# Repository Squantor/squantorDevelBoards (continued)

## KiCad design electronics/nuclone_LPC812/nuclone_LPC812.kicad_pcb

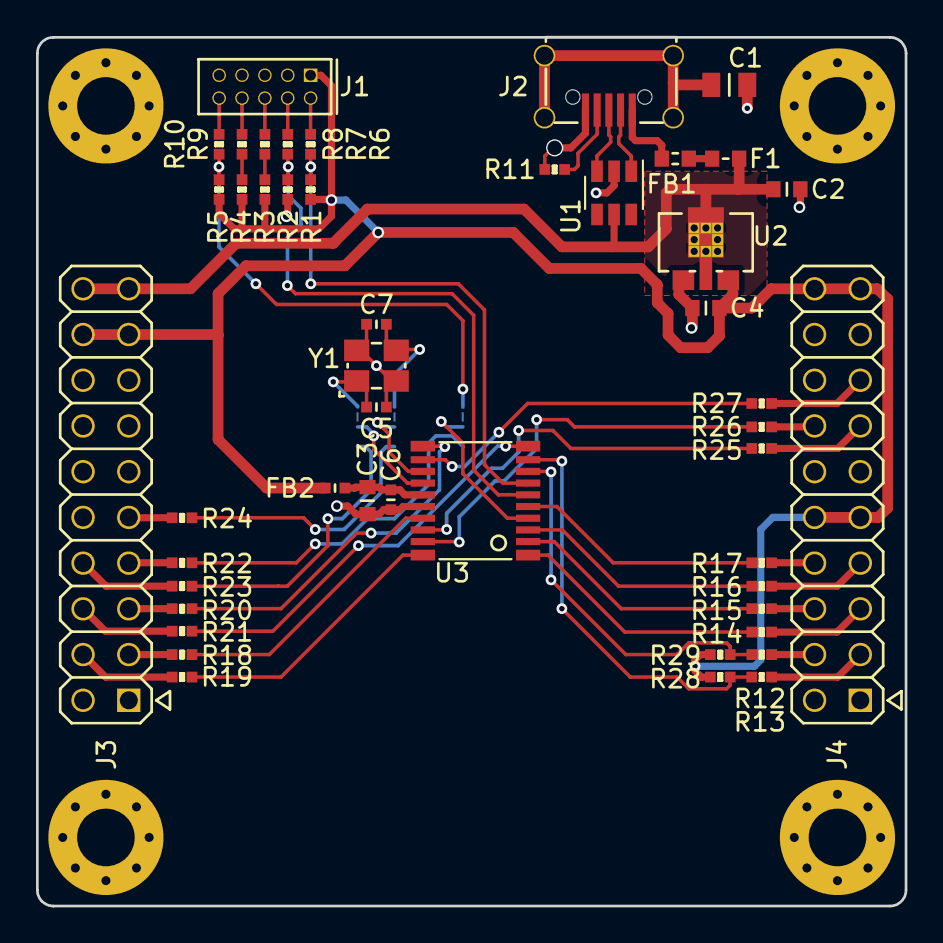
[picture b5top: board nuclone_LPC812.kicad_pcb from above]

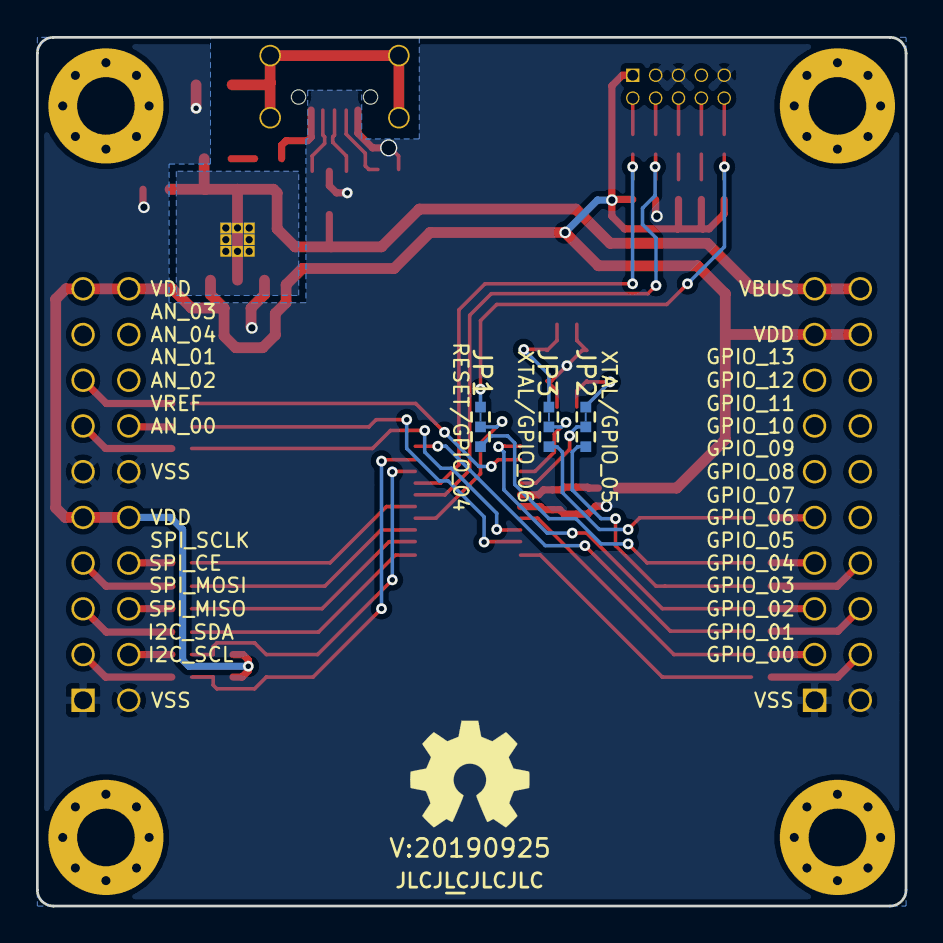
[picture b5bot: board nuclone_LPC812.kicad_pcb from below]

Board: 2 copper layers, 48.3 x 48.3 mm, 57 parts (6 on the bottom side), 57 nets.

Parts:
C1: 100n; C_0805
C2, C3, C4: 10u; C_0603
C5, C7: 18p; C_0402
C6: 1u; C_0402
F1: 0.5A; F_0603_hand
FB1: 100; L_0603
FB2: FB; C_0402
H1, H2, H3, H4: MountingHole; MountingHole_3.2mm_M3_Pad_Via
J1: JTAG_2X05; Header-0127-2X05-H006
J2: USB-ID; USB-muB-SMD_TH
J3: nuclone_20pin_gpio; Nuclone_20pin_gpio
J4: nuclone_20pin_bus_analog; Nuclone_20pin_bus_analog
JP1: RESET/GPIO_04; solder_jumper_3way_23conn
JP2: XTAL/GPIO_05; solder_jumper_3way_23conn
JP3: XTAL/GPIO_06; solder_jumper_3way_23conn
N1: OHWLOGO; OSHW-Symbol_6.7x6mm_SilkScreen
N2: 20190925; Label_version
N3: JLCJLCJLCJLC; Label_Generic
R1, R4: 100K; R_0402_hand
R2, R3, R5: 100k; R_0402_hand
R6, R7, R8, R9, R10, R12, R13, R14, R15, R16, R17, R18, R19, R20, R21, R22, R23, R24, R25, R26, R27: 100; R_0402_hand
R11: 0; R_0402_hand
R28, R29: 2.2K; R_0402_hand
U1: USBLC6-2; SOT23-6-HAND
U2: MCP1702-MB; SOT89-SOT23-Dual-NXP
U3: LPC812M101JDH20; SOT360
Y1: 12MHz; Crystal_3225_4

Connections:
/AN_00: J4.14, R26.2
/AN_01: J4.15, R27.2
/GPIO_00: J3.3, R18.2
/GPIO_01: J3.4, R19.2
/GPIO_02: J3.5, R20.2
/GPIO_03: J3.6, R21.2
/GPIO_04: J3.7, R22.2
/GPIO_05: J3.8, R23.2
/GPIO_06: J3.9, R24.2
/I2C_SCL: J4.4, R13.2
/I2C_SDA: J4.3, R12.2
/Jtag connector/TDI: R4.2, R9.2
/LPC812M101JD20 base/GPIO_04_INT: JP1.1, R22.1
/LPC812M101JD20 base/GPIO_05_INT: JP2.1, R23.1
/LPC812M101JD20 base/GPIO_06_INT: JP3.1, R24.1
/LPC812M101JD20 base/PIO0_0: R26.1, U3.19
/LPC812M101JD20 base/PIO0_1: R27.1, U3.12
/LPC812M101JD20 base/PIO0_4: R17.1, U3.5
/LPC812M101JD20 base/PIO0_5: JP1.2, U3.4
/LPC812M101JD20 base/PIO0_6: R25.1, U3.18
/LPC812M101JD20 base/PIO0_7: R18.1, U3.17
/LPC812M101JD20 base/PIO0_8: JP2.2, U3.14
/LPC812M101JD20 base/PIO0_9: JP3.2, U3.13
/LPC812M101JD20 base/PIO0_10: R12.1, R28.2, U3.9
/LPC812M101JD20 base/PIO0_11: R13.1, R29.2, U3.8
/LPC812M101JD20 base/PIO0_12: R16.1, U3.3
/LPC812M101JD20 base/PIO0_13: R15.1, U3.2
/LPC812M101JD20 base/PIO0_14: R19.1, U3.20
/LPC812M101JD20 base/PIO0_15: R20.1, U3.11
/LPC812M101JD20 base/PIO0_16: R21.1, U3.10
/LPC812M101JD20 base/PIO0_17: R14.1, U3.1
/LPC812M101JD20 base/XTAL_IN: C5.1, JP2.3, Y1.1
/LPC812M101JD20 base/XTAL_OUT: C7.1, JP3.3, Y1.3
/MCU_RESET: JP1.3, R5.2, R10.2
/MCU_TCK: R2.2, R7.2, U3.6
/MCU_TDO: R3.2, R8.2
/MCU_TMS: R1.2, R6.2, U3.7
/SPI_CE: J4.8, R17.2
/SPI_MISO: J4.6, R15.2
/SPI_MOSI: J4.5, R14.2
/SPI_SCLK: J4.7, R16.2
/USB input/USB_IN_D+: J2.3, U1.3
/USB input/USB_IN_D-: J2.2, U1.1
/VBUS: C2.1, F1.1, J3.19, J3.20, U1.5, U2.2
/VDD: C4.1, FB2.2, J1.1, J3.17, J3.18, J4.9, J4.10, J4.19, J4.20, R1.1, R3.1, R4.1, R5.1, R28.1, R29.1, U2.3
/VREF: J4.13, R25.2
unnamed: C1.1, J2.S
unnamed: C3.1, C6.1, FB2.1, U3.15
unnamed: F1.2, FB1.1
unnamed: FB1.2, J2.1
unnamed: J1.2, R6.1
unnamed: J1.4, R7.1
unnamed: J1.6, R8.1
unnamed: J1.8, R9.1
unnamed: J1.10, R10.1
unnamed: J2.4, R11.1
VSS: C1.2, C2.2, C3.2, C4.2, C5.2, C6.2, C7.2, J1.3, J1.5, J1.9, J2.5, J3.1, J3.2, J4.1, J4.2, J4.11, J4.12, R2.1, R11.2, U1.2, U2.1, U3.16, Y1.2, Y1.4

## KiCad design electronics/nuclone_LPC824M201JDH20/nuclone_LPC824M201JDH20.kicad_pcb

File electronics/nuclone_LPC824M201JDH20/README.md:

# Nuclone for the LPC824M201JDH20 microcontroller
Small nuclone development kit for the [LPC824M201JDH20](https://www.nxp.com/products/processors-and-microcontrollers/arm-microcontrollers/general-purpose-mcus/lpc800-cortex-m0-plus-/low-cost-microcontrollers-mcus-based-on-arm-cortex-m0-plus-cores:LPC82X) microcontroller.
# HSI (Hardware Software Interface)
* PIO0_2 is the SWDIO/TMS pin but there is a default open jumper to a header pin
* PIO0_3 is the SWCLK/TCK pin but there is a default open jumper to a header pin
* PIO0_5 is the RESET pin but there is a default open jumper to a header pin
* PIO0_8 is the XTALIN pin but there is a default closed jumper to a header pin
* PIO0_9 is the XTALIN pin but there is a default closed jumper to a header pin
* VREFP is connected to VDD via a 600Ohm ferrite bead
* Crystal frequency is 12MHz in a 3225 package
## TODO's
Still some things need to be done:
* Produce at [JLCPCB](https://jlcpcb.com/)
* Assemble
* Test & characterise
* update Readme.md with pictures and BOM
## BOM
* [LPC824M201JDH20](https://lcsc.com/product-detail/NXP-MCU_NXP_LPC824M201JDH20_LPC824M201JDH20_C86812.html)

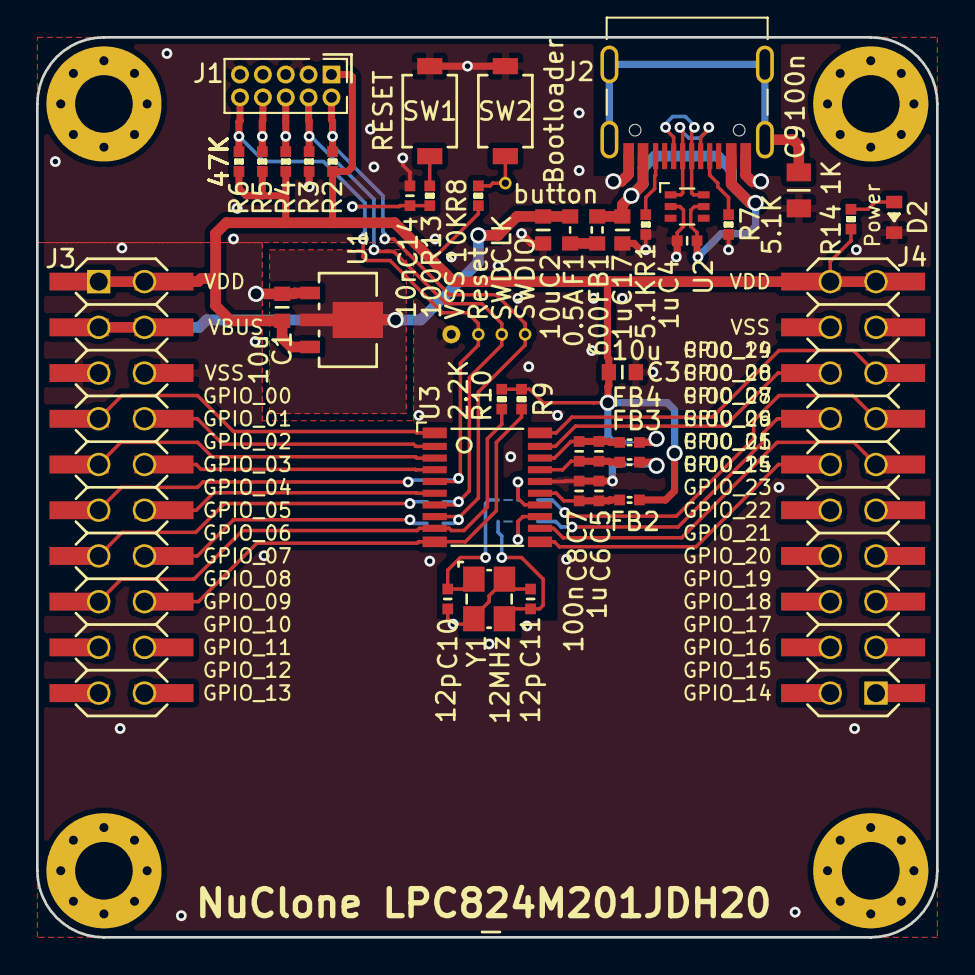
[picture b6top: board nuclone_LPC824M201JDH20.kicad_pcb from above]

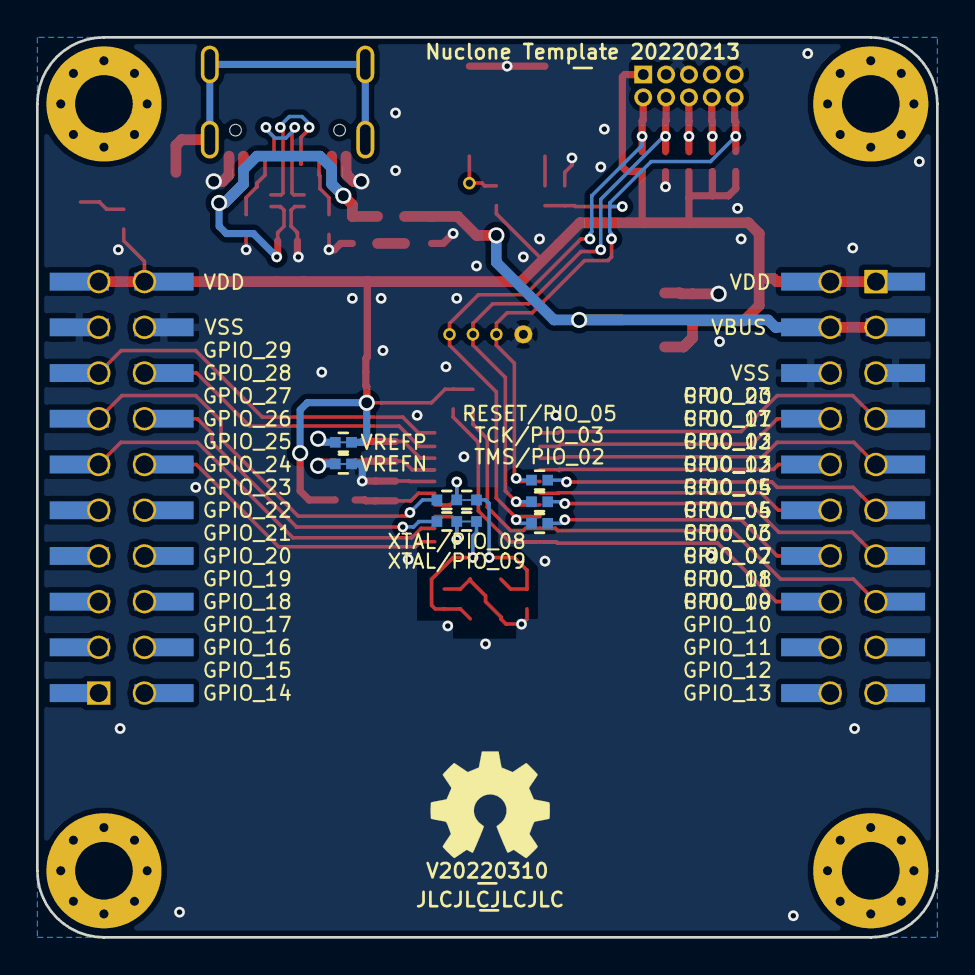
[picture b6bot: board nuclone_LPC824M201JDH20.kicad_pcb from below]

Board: 2 copper layers, 50.0 x 50.0 mm, 62 parts (11 on the bottom side), 43 nets.

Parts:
C1, C2, C3: 10u; C_0603
C4, C5, C6: 1u; C_0402
C7, C8: 100n; C_0402
C9: 100n; C_0805
C10, C11: 12p; C_0402
C14: 10n; C_0402
C17: 1u; C_0603
D2: GREEN; LED_0603_hand
F1: 0.5A; F_0603_hand
FB1: 600; L_0603
FB2, FB3, FB4: 600; L_0402
H1, H2, H3, H4: MountingHole; MountingHole_3.2mm_M3_Pad_Via
J1: JTAG_2X05; Header-0127-2X05-H006
J2: TYPE-C-31-M-12; USB-C-HRO-31-M-12
J3: nuclone_small_left; nuclone_small_left_stacked
J4: nuclone_small_right; nuclone_small_right_stacked
JP1: TMS/PIO_02; solder_jumper_0402_2way_noconn
JP2: TCK/PIO_03; solder_jumper_0402_2way_noconn
JP3: RESET/PIO_05; solder_jumper_0402_2way_noconn
JP4: VREFP; solder_jumper_0402_2way_conn
JP5: VREFN; solder_jumper_0402_2way_conn
JP6: XTAL/PIO_08; solder_jumper_0402_3way_12conn
JP7: XTAL/PIO_09; solder_jumper_0402_3way_12conn
N1: OHWLOGO; OSHW-Symbol_6.7x6mm_SilkScreen
N2: V20220310; Label_Generic
N3: JLCJLCJLCJLC; Label_Generic
N4: NuClone LPC824M201JDH20; Label_Generic
N5: Nuclone Template 20220213; Label_Generic
R1, R7: 5.1K; R_0402_hand
R2, R3, R4, R5, R6: 47K; R_0402_hand
R8: 10K; R_0402_hand
R9, R10: 2.2K; R_0402_hand
R13: 100; R_0402_hand
R14: 1K; R_0402_hand
SW1: RESET; TD-85XU
SW2: Bootloader; TD-85XU
TP1: SWDIO; TestPoint_hole_H04R07
TP2: SWDCLK; TestPoint_hole_H04R07
TP3: VSS; TestPoint_hole_H05R10
TP4: button; TestPoint_hole_H04R07
TP5: Reset; TestPoint_hole_H04R07
U1: MCP1702-MB; SOT89-NXP
U2: TPESD0504C6; SOT363-ONsemi
U3: LPC824M201JDH20; SOT360-NXP
Y1: 12MHz; Crystal_3225_4

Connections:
/Bootloader: R8.1, SW2.2, TP4.1
/DN: J2.A7 (DN1), J2.B7 (DN2), U2.1 (IO_1)
/DP: J2.A6 (DP1), J2.B6 (DP2), U2.6 (IO_4)
/GPIO_00: J3.7 (GPIO_00), U3.1 (PIO0_23/ADC_3/ACMP_I4)
/GPIO_01: J3.8 (GPIO_01), U3.2 (PIO0_17/ADC_9)
/GPIO_02: J3.9 (GPIO_02), U3.3 (PIO0_13/ADC_10)
/GPIO_03: J3.10 (GPIO_03), U3.4 (PIO0_12)
/GPIO_04: J3.11 (GPIO_04), JP3.2
/GPIO_05: J3.12 (GPIO_05), U3.6 (PIO0_4/ADC_11/WAKEUP/TRST)
/GPIO_06: J3.13 (GPIO_06), JP2.2
/GPIO_07: J3.14 (GPIO_07), JP1.2
/GPIO_08: J3.15 (GPIO_08), R10.2, U3.9 (PIO0_11/I2C0_SDA)
/GPIO_09: J3.16 (GPIO_09), R9.2, U3.10 (PIO0_10/I2C0_SCL)
/GPIO_24: J4.12 (GPIO_24), U3.11 (PIO0_15)
/GPIO_25: J4.11 (GPIO_25), U3.12 (PIO0_1/ACMP_I2/CLKIN/TDI)
/GPIO_26: J4.14 (GPIO_26), JP7.3
/GPIO_27: J4.13 (GPIO_27), JP6.3
/GPIO_28: J4.16 (GPIO_28), U3.19 (PIO0_0/ACMP_I1/TDO)
/GPIO_29: J4.15 (GPIO_29), U3.20 (PIO0_14/ADC_2/ACMP_I3)
/RESET: C14.2, J1.10 (nRESET), JP3.1, R6.1, R13.1, TP5.1, U3.5 (RESET/PIO0_5)
/TCK: J1.4 (SWDCLK/TCK), JP2.1, R3.1, TP2.1, U3.7 (SWCLK/PIO0_3/TCK)
/TDI: J1.8 (TDI), R5.1
/TDO: J1.6 (SWO/TDO), R4.1
/TMS: J1.2 (SWDIO/TMS), JP1.1, R2.1, TP1.1, U3.8 (SWDIO/PIO0_2/TMS)
/VBUS: C2.2, F1.1, J3.3 (VBUS), J3.4 (VBUS), U1.2 (Vin)
/VDD: C1.1, C3.1, FB2.2, J1.1 (VCC), J3.1 (VDD), J3.2 (VDD), J4.19 (VDD), J4.20 (VDD), JP4.1, R2.2, R4.2, R5.2, R6.2, R8.2, R9.1, R10.1, R14.2, U1.3 (Vout)
/VSS: C1.2, C2.1, C3.2, C4.2, C5.2, C7.2, C9.1, C10.2, C11.2, C14.1, C17.1, D2.1 (K), J1.3 (GND), J1.5 (GND), J1.9 (GNDDET), J2.A1B12 (GND), J2.B1A12 (GND), J3.5 (VSS), J3.6 (VSS), J4.17 (VSS), J4.18 (VSS), JP5.1, R1.1, R3.2, R7.1, SW1.1, SW2.1, TP3.1, U1.1 (GND), U2.2 (VSS), U3.16 (VSS), Y1.2, Y1.4
/VUSB: C4.1, C17.2, FB1.2, J2.A4B9 (VBUS), J2.B4A9 (VBUS), U2.5 (VDD)
/microcontroller/VDDA: FB3.2, JP4.2
/microcontroller/VSSA: FB4.2, JP5.2
/microcontroller/XTALIN: JP6.2, U3.14 (PIO0_8/XTALIN)
/microcontroller/XTALOUT: JP7.2, U3.13 (PIO0_9/XTALOUT)
unnamed: C5.1, C7.1, FB2.1, U3.15 (VDD)
unnamed: C6.1, C8.1, FB3.1, U3.18 (VREFP)
unnamed: C6.2, C8.2, FB4.1, U3.17 (VREFN)
unnamed: C9.2, J2.S (Shield)
unnamed: C10.1, JP6.1, Y1.1
unnamed: C11.1, JP7.1, Y1.3
unnamed: D2.2 (A), R14.1
unnamed: F1.2, FB1.1
unnamed: J2.A5 (CC1), R7.2
unnamed: J2.B5 (CC2), R1.2
unnamed: R13.2, SW1.2
